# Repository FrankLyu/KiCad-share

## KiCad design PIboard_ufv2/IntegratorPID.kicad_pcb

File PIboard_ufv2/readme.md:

The hopefully final design works. With everything unchanged, the bandwidth is a bit low, only 2.5 kHz for full integral.

Now I changed the resistor for AD8429 to 680 Ohm, so the BW is now 5 kHz. (With default, it is 1.5kOhm, probably too large)

The test sequence:
First change TP-1H to very high, and change TP-1L to very low. Then with 50 Ohm ended on setpoint, another arm with controllable input:
	1. Check on TP4 the diff amp works.
	2. Short J12, check pure P works at TP5.
	3. Short J4, disconnect J12. It is a pure I. check it locks to itself.
	4. Solder bourns 1,2,3 pin to down, middle, and up pins.
	5. Change R32 to 10k if you want the manual out to start from 0 V, instead of some negative value.
	
Simple and nice!

There is a bug. The input signalIn and Setpoint are connected. When locked, SP is high but RF switch is overridden, then SignalIn (measurement) will be a non-zero value! When not locked, SP is low and manual out is high s.t. signalin is high, the measurement may be trimmed by the low SP. 
It can go to at most 4 V. However, if the SP is floating it will be okay?

Next version, we can Change R32 to a place where it is easier to resolder. It sets the lower limit of the manual output.

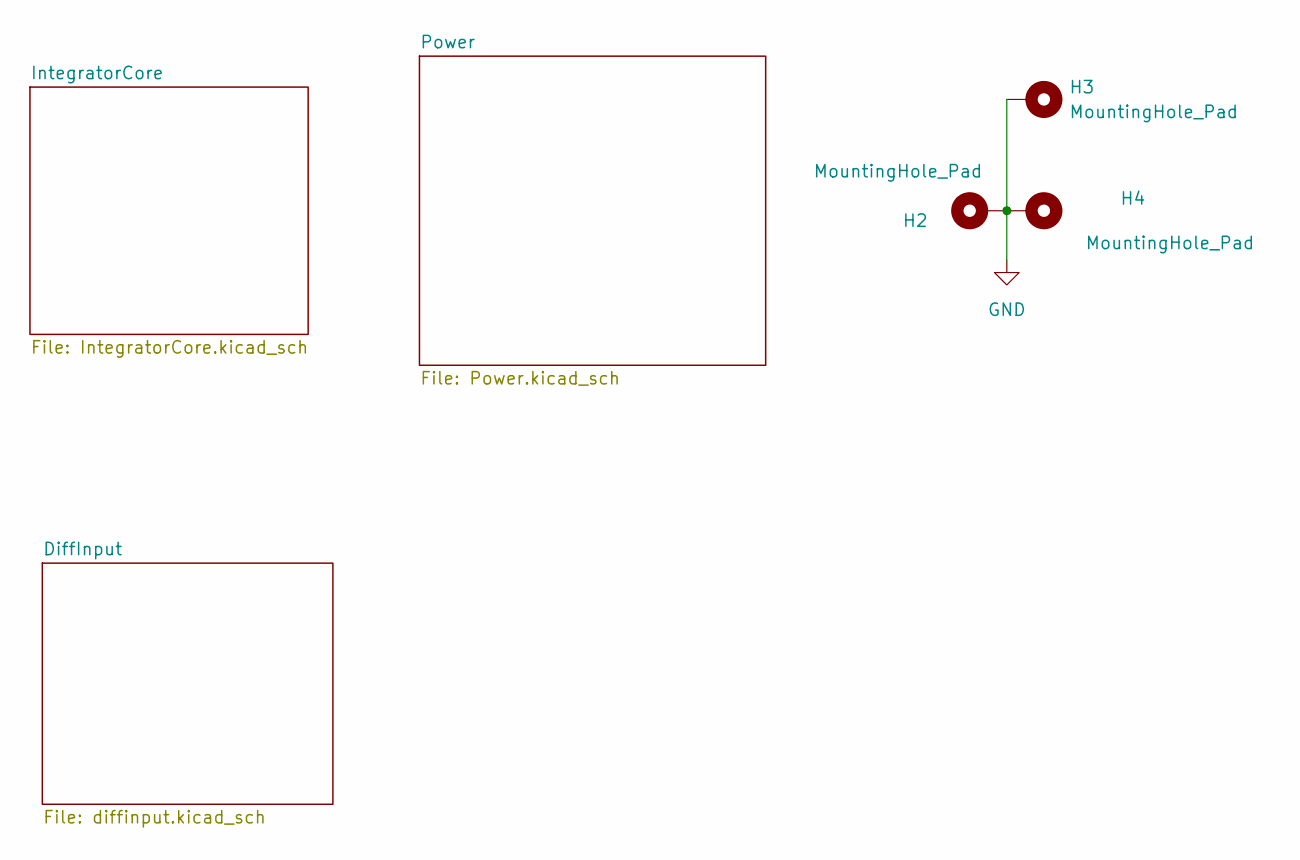
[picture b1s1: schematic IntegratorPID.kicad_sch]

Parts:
H2, H3, H4: MountingHole_Pad; MountingHole_3.7mm_Pad_Via

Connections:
GND: H2.1, H3.1, H4.1; also elsewhere on the board

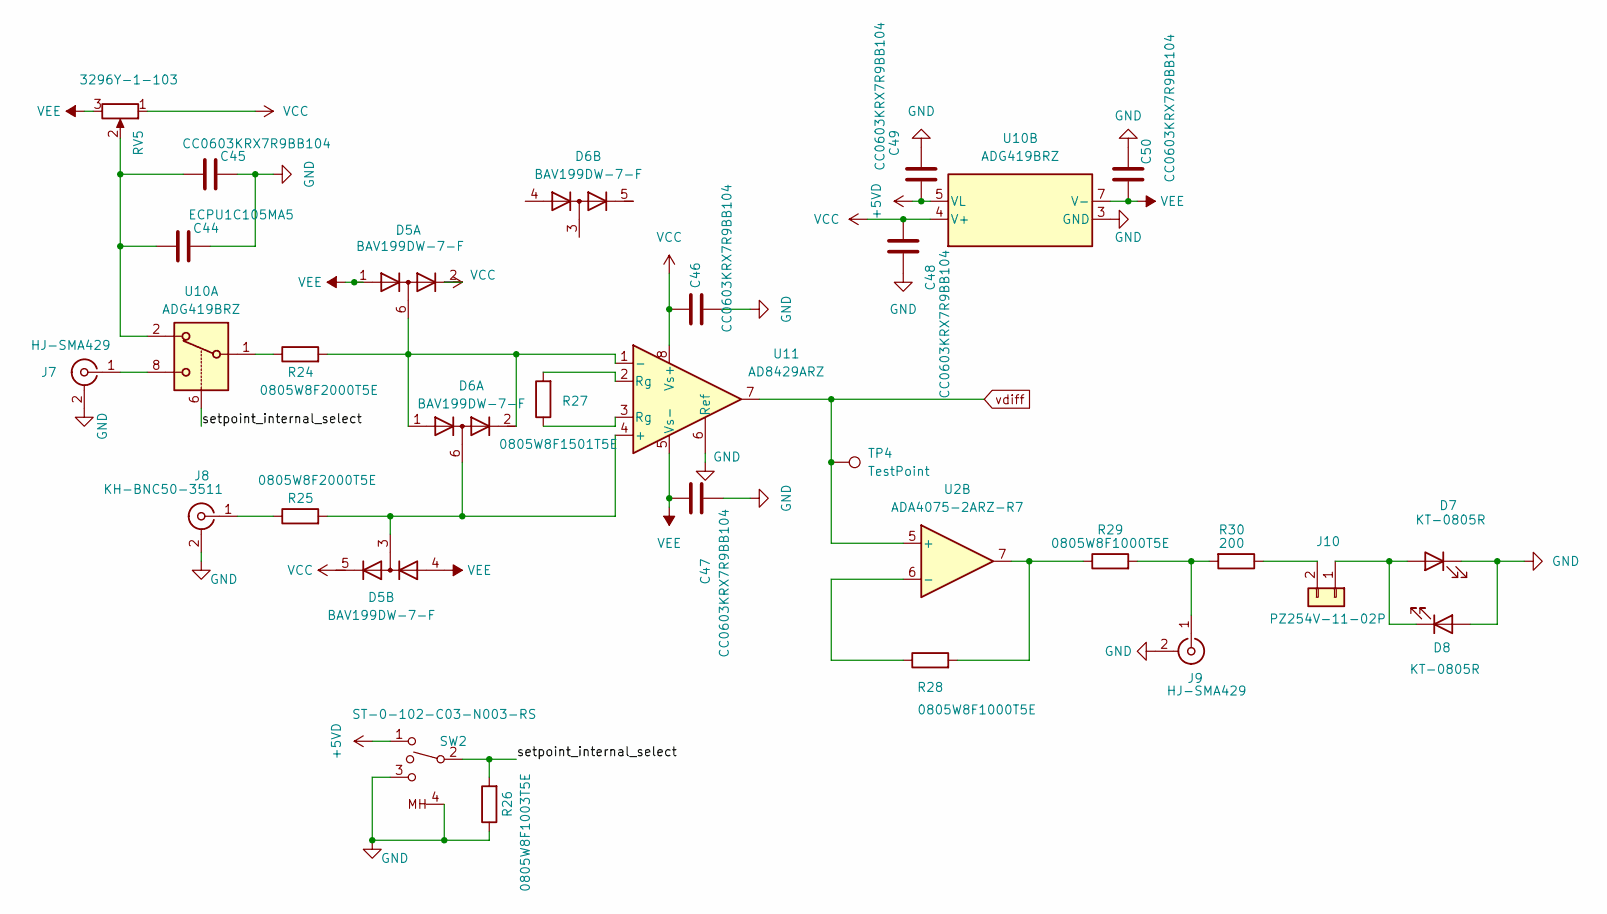
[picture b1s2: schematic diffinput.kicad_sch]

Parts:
C44: ECPU1C105MA5; C_1210_3225Metric_Pad1.33x2.70mm_HandSolder
C45, C46, C47, C48, C49, C50: CC0603KRX7R9BB104; C_0603_1608Metric_Pad1.08x0.95mm_HandSolder
D5, D6: BAV199DW-7-F; SOT-363_SC-70-6
D7, D8: KT-0805R; D_0805_2012Metric_Pad1.15x1.40mm_HandSolder
J7, J9: HJ-SMA429; SMA_Amphenol_132134_Vertical
J8: KH-BNC50-3511; BNC_Amphenol_B6252HB-NPP3G-50_Horizontal
J10: PZ254V-11-02P; PinHeader_1x02_P2.54mm_Vertical
R24, R25: 0805W8F2000T5E; R_0805_2012Metric
R26: 0805W8F1003T5E; R_0805_2012Metric
R27: 0805W8F1501T5E; R_0805_2012Metric
R28, R29: 0805W8F1000T5E; R_0805_2012Metric
R30: 200; R_0805_2012Metric
RV5: 3296Y-1-103; Potentiometer_Bourns_3296Y_Vertical
SW2: ST-0-102-C03-N003-RS; SW_SPDT_ST-0-103-C03-N003-RS
TP4: TestPoint; TestPoint_Pad_D1.0mm
U2: ADA4075-2ARZ-R7; SOIC-8_3.9x4.9mm_P1.27mm
U10: ADG419BRZ; SOIC-8_3.9x4.9mm_P1.27mm
U11: AD8429ARZ; SOIC-8_3.9x4.9mm_P1.27mm

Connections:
+5VD: C49.2, SW2.1, U10.5 (VL); also elsewhere on the board
/DiffInput/setpoint_internal_select: R26.2, SW2.2, U10.6
GND: C44.2, C45.2, C46.1, C47.1, C48.1, C49.1, C50.2, D7.1 (K), D8.2 (A), J7.2 (Ext), J8.2 (Ext), J9.2 (Ext), R26.1, SW2.3, SW2.4 (MH), U10.3 (GND), U11.6 (Ref); also elsewhere on the board
unnamed: C44.1, C45.1, RV5.2, U10.2
unnamed: D5.6 (K3A4), D6.1 (A1), D6.2 (K2), R24.2, U11.1 (-)
unnamed: D5.3 (K1A2), D6.6 (K3A4), R25.2, U11.4 (+)
unnamed: D7.2 (A), D8.1 (K), J10.1
unnamed: J7.1 (In), U10.8
unnamed: J8.1 (In), R25.1
unnamed: J9.1 (In), R29.2, R30.2
unnamed: J10.2, R30.1
unnamed: R24.1, U10.1
unnamed: R27.1, U11.3 (Rg)
unnamed: R27.2, U11.2 (Rg)
unnamed: R28.2, R29.1, U2.7
unnamed: R28.1, U2.6 (-)
VCC: C46.2, C48.2, D5.2 (K2), D5.5 (K4), RV5.1, U10.4 (V+), U11.8 (Vs+); also elsewhere on the board
VEE: C47.2, C50.1, D5.1 (A1), D5.4 (A3), RV5.3, U10.7 (V-), U11.5 (Vs-); also elsewhere on the board
vdiff: TP4.1, U2.5 (+), U11.7; also elsewhere on the board

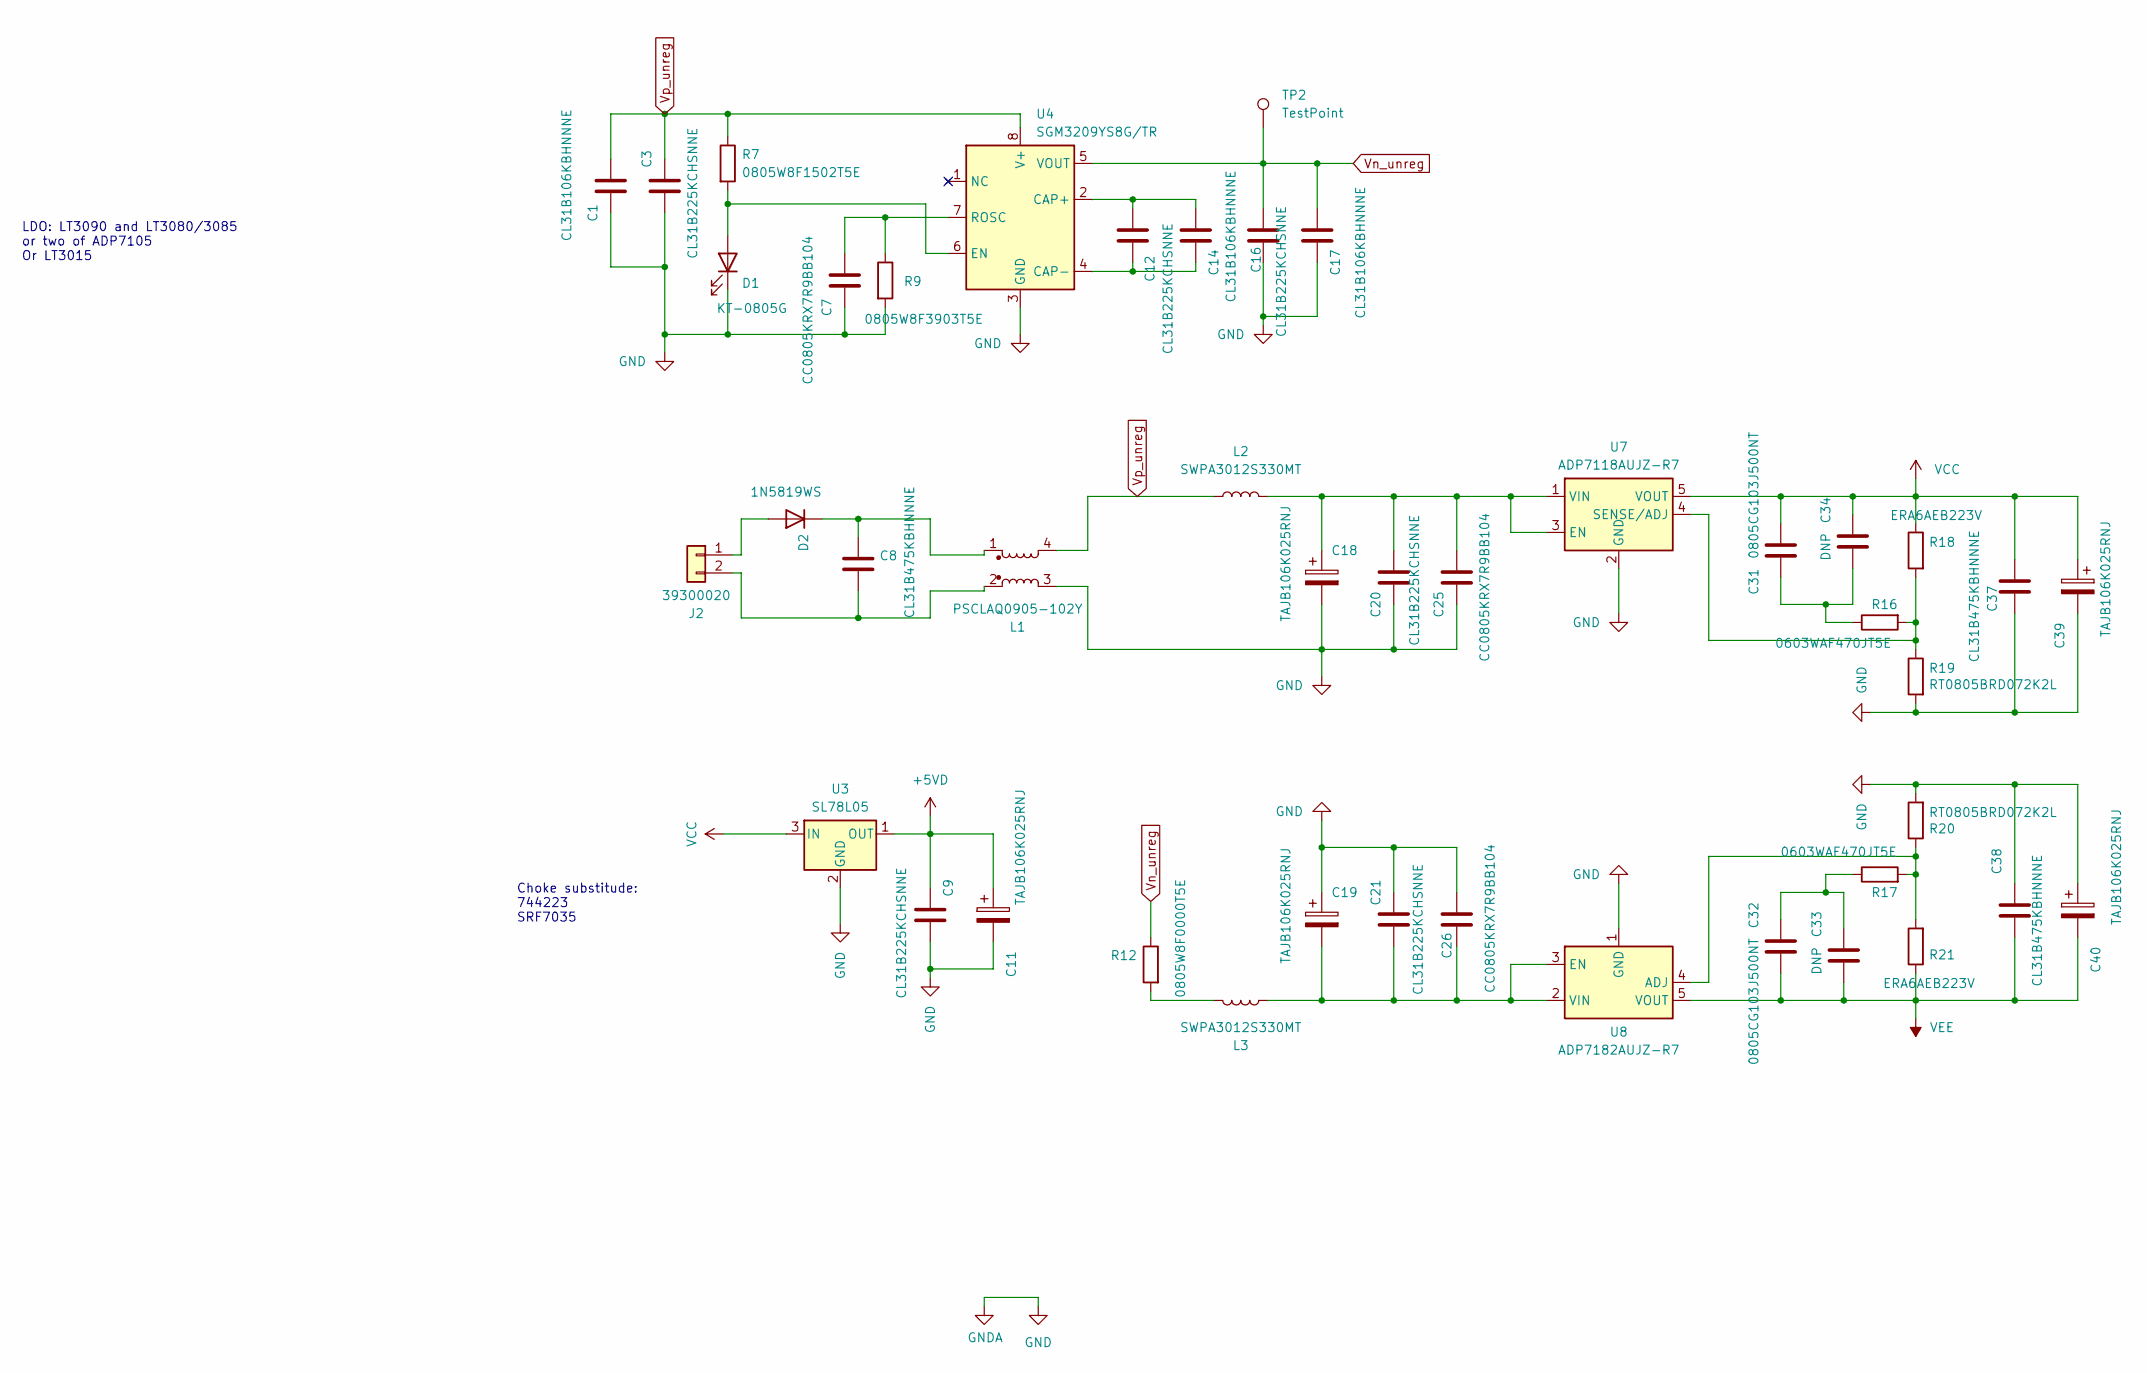
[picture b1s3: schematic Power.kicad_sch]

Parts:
C1, C14, C17: CL31B106KBHNNNE; C_1206_3216Metric_Pad1.33x1.80mm_HandSolder
C3, C9, C12, C16, C20, C21: CL31B225KCHSNNE; C_1206_3216Metric_Pad1.33x1.80mm_HandSolder
C7, C25, C26: CC0805KRX7R9BB104; C_0805_2012Metric
C8, C37, C38: CL31B475KBHNNNE; C_1206_3216Metric_Pad1.33x1.80mm_HandSolder
C11, C18, C19, C39, C40: TAJB106K025RNJ; CP_EIA-3528-15_AVX-H
C31, C32: 0805CG103J500NT; C_0805_2012Metric
C33, C34: DNP; C_0805_2012Metric
D1: KT-0805G; D_0805_2012Metric_Pad1.15x1.40mm_HandSolder
D2: 1N5819WS; D_SOD-323_HandSoldering
J2: 39300020; 39-30-Y020
L1: PSCLAQ0905-102Y; SRF0905501Y
L2, L3: SWPA3012S330MT; L_Taiyo-Yuden_MD-3030
R7: 0805W8F1502T5E; R_0805_2012Metric
R9: 0805W8F3903T5E; R_0805_2012Metric
R12: 0805W8F0000T5E; R_0805_2012Metric
R16, R17: 0603WAF470JT5E; R_0603_1608Metric_Pad0.98x0.95mm_HandSolder
R18, R21: ERA6AEB223V; R_0805_2012Metric
R19, R20: RT0805BRD072K2L; R_0805_2012Metric
TP2: TestPoint; TestPoint_Pad_D1.5mm
U3: SL78L05; SOT-89-3
U4: SGM3209YS8G/TR; SOIC-8_3.9x4.9mm_P1.27mm
U7: ADP7118AUJZ-R7; TSOT-23-5
U8: ADP7182AUJZ-R7; TSOT-23-5

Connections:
+5VD: C9.2, C11.1, U3.1 (OUT); also elsewhere on the board
GND: C1.2, C3.1, C7.2, C9.1, C11.2, C16.1, C17.2, C18.2, C19.1, C20.2, C21.2, C25.2, C26.2, C37.2, C38.2, C39.2, C40.1, D1.1 (K), L1.3, R9.2, R19.2, R20.2, U3.2 (GND), U4.3 (GND), U7.2 (GND), U8.1 (GND); also elsewhere on the board
unnamed: C31.2, C34.1, R16.1
unnamed: C32.2, C33.2, R17.1
unnamed: D1.2 (A), R7.2, U4.6 (EN)
unnamed: D2.2 (A), J2.1
unnamed: C8.1, D2.1 (K), L1.1
unnamed: C8.2, J2.2, L1.2
unnamed: L3.1, R12.2
unnamed: C12.2, C14.1, U4.2 (CAP+)
unnamed: C12.1, C14.2, U4.4 (CAP-)
unnamed: C7.1, R9.1, U4.7 (ROSC)
unnamed: C18.1, C20.1, C25.1, L2.2, U7.1 (VIN), U7.3 (EN)
unnamed: R16.2, R18.2, R19.1, U7.4 (SENSE/ADJ)
unnamed: R17.2, R20.1, R21.2, U8.4 (ADJ)
unnamed: C19.2, C21.1, C26.1, L3.2, U8.2 (VIN), U8.3 (EN)
VCC: C31.1, C34.2, C37.1, C39.1, R18.1, U3.3 (IN), U7.5 (VOUT); also elsewhere on the board
VEE: C32.1, C33.1, C38.1, C40.2, R21.1, U8.5 (VOUT); also elsewhere on the board
Vn_unreg: C16.2, C17.1, R12.1, TP2.1, U4.5 (VOUT)
Vp_unreg: C1.1, C3.2, L1.4, L2.1, R7.1, U4.8 (V+)

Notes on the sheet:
Choke substitude: 744223 SRF7035
LDO: LT3090 and LT3080/3085 or two of ADP7105 Or LT3015

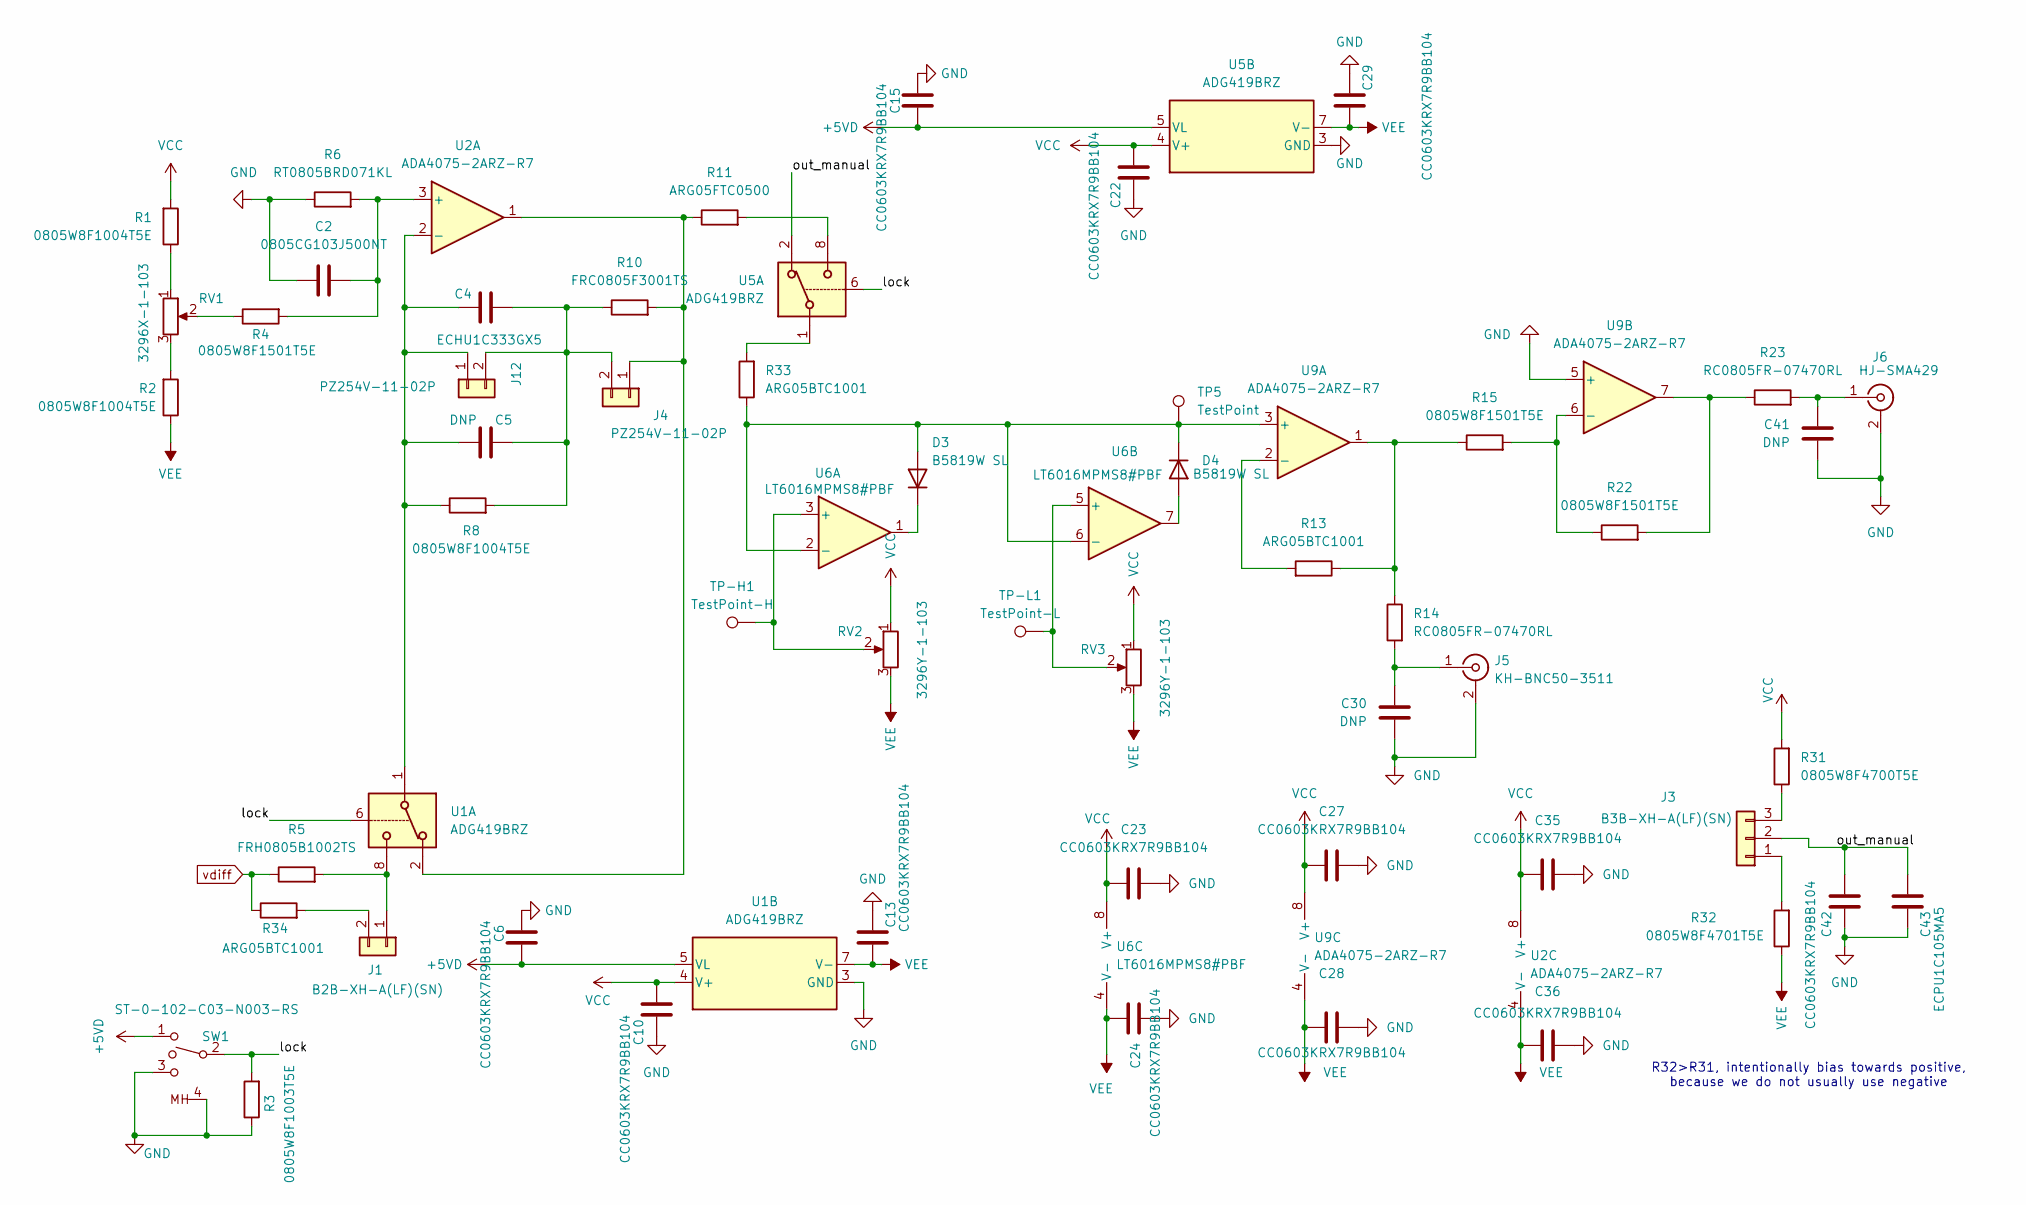
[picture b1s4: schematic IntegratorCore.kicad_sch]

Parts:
C2: 0805CG103J500NT; C_0805_2012Metric
C4: ECHU1C333GX5; C_1206_3216Metric
C5: DNP; C_2225_5664Metric_Pad1.80x6.60mm_HandSolder
C6, C10, C13, C15, C22, C23, C24, C27, C28, C29, C35, C36, C42: CC0603KRX7R9BB104; C_0603_1608Metric_Pad1.08x0.95mm_HandSolder
C30, C41: DNP; C_0805_2012Metric
C43: ECPU1C105MA5; C_1210_3225Metric_Pad1.33x2.70mm_HandSolder
D3, D4: B5819W SL; D_SOD-123
J1: B2B-XH-A(LF)(SN); JST_XH_B2B-XH-A_1x02_P2.50mm_Vertical
J3: B3B-XH-A(LF)(SN); JST_XH_B3B-XH-A_1x03_P2.50mm_Vertical
J4, J12: PZ254V-11-02P; PinHeader_1x02_P2.54mm_Vertical
J5: KH-BNC50-3511; BNC_Amphenol_B6252HB-NPP3G-50_Horizontal
J6: HJ-SMA429; SMA_Amphenol_132134_Vertical
R1, R2, R8: 0805W8F1004T5E; R_0805_2012Metric
R3: 0805W8F1003T5E; R_0805_2012Metric
R4, R15, R22: 0805W8F1501T5E; R_0805_2012Metric
R5: FRH0805B1002TS; R_0805_2012Metric
R6: RT0805BRD071KL; R_0805_2012Metric
R10: FRC0805F3001TS; R_0805_2012Metric
R11: ARG05FTC0500; R_0805_2012Metric
R13, R33, R34: ARG05BTC1001; R_0805_2012Metric
R14, R23: RC0805FR-07470RL; R_0805_2012Metric
R31: 0805W8F4700T5E; R_0805_2012Metric
R32: 0805W8F4701T5E; R_0805_2012Metric
RV1: 3296X-1-103; Potentiometer_Bourns_3296X_Horizontal
RV2, RV3: 3296Y-1-103; Potentiometer_Bourns_3296Y_Vertical
SW1: ST-0-102-C03-N003-RS; SW_SPDT_ST-0-103-C03-N003-RS
TP5: TestPoint; TestPoint_Pad_D1.0mm
TP-H1: TestPoint-H; TestPoint_Pad_D1.0mm
TP-L1: TestPoint-L; TestPoint_Pad_D1.0mm
U1, U5: ADG419BRZ; SOIC-8_3.9x4.9mm_P1.27mm
U2, U9: ADA4075-2ARZ-R7; SOIC-8_3.9x4.9mm_P1.27mm
U6: LT6016MPMS8#PBF; MSOP-8_3x3mm_P0.65mm

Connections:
+5VD: C6.2, C15.2, SW1.1, U1.5 (VL), U5.5 (VL); also elsewhere on the board
/IntegratorCore/lock: R3.2, SW1.2, U1.6, U5.6
/IntegratorCore/out_manual: C42.1, C43.1, J3.2, U5.2
GND: C2.1, C6.1, C10.2, C13.2, C15.1, C22.2, C23.1, C24.1, C27.1, C28.1, C29.2, C30.1, C35.1, C36.1, C41.1, C42.2, C43.2, J5.2 (Ext), J6.2 (Ext), R3.1, R6.1, SW1.3, SW1.4 (MH), U1.3 (GND), U5.3 (GND), U9.5 (+); also elsewhere on the board
unnamed: D3.2 (A), D4.1 (K), R33.1, TP5.1, U6.2 (-), U6.6 (-), U9.3 (+)
unnamed: D3.1 (K), U6.1
unnamed: D4.2 (A), U6.7
unnamed: J1.1, R5.2, U1.8
unnamed: J1.2, R34.2
unnamed: J3.1, R32.2
unnamed: J3.3, R31.1
unnamed: J4.1, R10.2, R11.1, U1.2, U2.1
unnamed: C30.2, J5.1 (In), R14.2
unnamed: C41.2, J6.1 (In), R23.2
unnamed: C4.1, C5.1, J12.1, R8.1, U1.1, U2.2 (-)
unnamed: C4.2, C5.2, J4.2, J12.2, R8.2, R10.1
unnamed: R1.1, RV1.1
unnamed: R2.2, RV1.3
unnamed: R4.1, RV1.2
unnamed: R11.2, U5.8
unnamed: R13.1, R14.1, R15.1, U9.1
unnamed: R22.2, R23.1, U9.7
unnamed: R33.2, U5.1
unnamed: C2.2, R4.2, R6.2, U2.3 (+)
unnamed: RV2.2, TP-H1.1, U6.3 (+)
unnamed: RV3.2, TP-L1.1, U6.5 (+)
unnamed: R13.2, U9.2 (-)
unnamed: R15.2, R22.1, U9.6 (-)
VCC: C10.1, C22.1, C23.2, C27.2, C35.2, R1.2, R31.2, RV2.1, RV3.1, U1.4 (V+), U2.8 (V+), U5.4 (V+), U6.8 (V+), U9.8 (V+); also elsewhere on the board
VEE: C13.1, C24.2, C28.2, C29.1, C36.2, R2.1, R32.1, RV2.3, RV3.3, U1.7 (V-), U2.4 (V-), U5.7 (V-), U6.4 (V-), U9.4 (V-); also elsewhere on the board
vdiff: R5.1, R34.1; also elsewhere on the board

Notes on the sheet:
R32>R31, intentionally bias towards positive, because we do not usually use negative

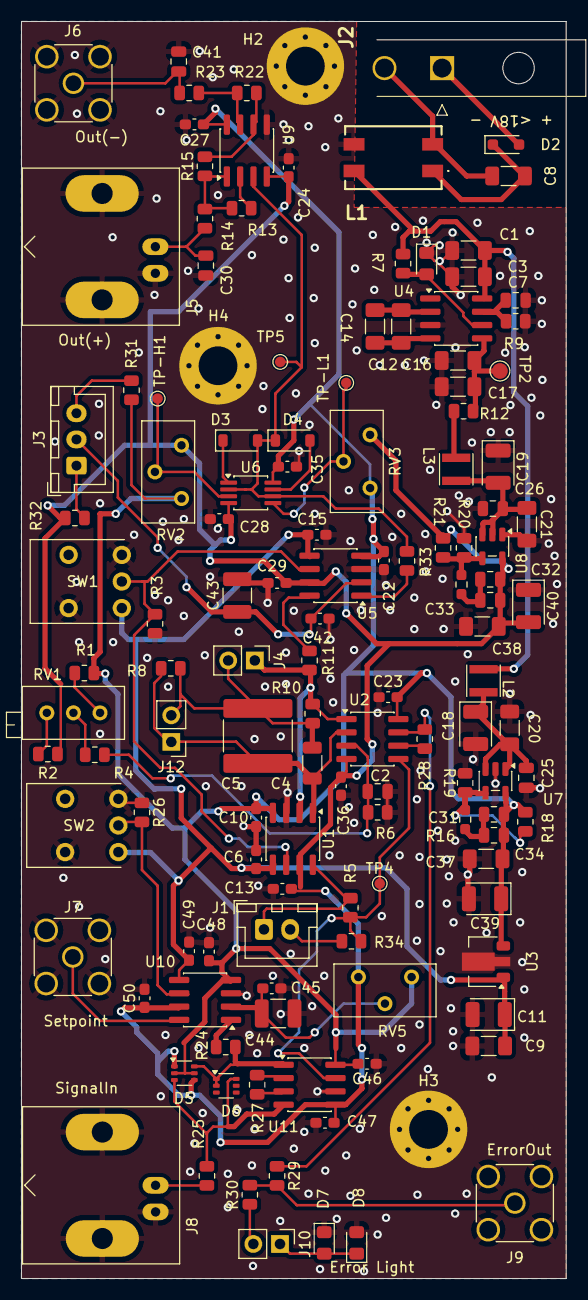
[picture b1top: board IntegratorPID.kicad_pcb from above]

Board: 4 copper layers, 52.0 x 120.0 mm, 131 parts (0 on the bottom side), 61 nets.

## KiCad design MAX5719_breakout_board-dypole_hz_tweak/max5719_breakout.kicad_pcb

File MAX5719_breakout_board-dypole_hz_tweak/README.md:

Teensy MAX5719 high-resolution (low-speed) AWG v1 in dypole. Problems are at the bottom of the file.

Interface is via SPI, all microcontroller signals are isolated using MAX14850ASE (or compatible) capacitive isolator. A galvanically isolated power supply may be used to provide the +/-15V DAC/analog buffer supply, so microcontroller USB does not need to be isolated.
Tested up to 20MHz SPI on a breadboard, good layout of microcontroller to breakout board PCB may allow for higher speeds (MAX5719 is specified up to 50MHz).

Onboard 5 V voltage reference, output is then scaled up by 2.0x for a 10V range.

JP1 is for unipolar output. JP2/3 for bipolar.

We chose Op Amp OP2192. Voltage reference chip MAX6126 (which has a demo schematic for MAX5719). The exact voltages on board should be +13.2, -13.2 and +5.376 V.

Production (purchased at JLCPCB) on Sep 9th 2025. This version has 3 problems. 

First, the zero resistors are not soldered. The voltage divider (resistor) for ADP7118 5 V is wrong.

Second, the +13.2 V and -13.2 V fight each other. Negative prevents positive voltage from turning on. This might be the safe feature of ADP7118. After taking away the OP2192, the problem is gone.

Third, the BNC connector is not well shielded, and it picks up high frequency (>10 MHz RF) from the air.

To address the second problem, we go back to LM7812, LM7912 to power the Op amp. It doesn't affect the noise performance.

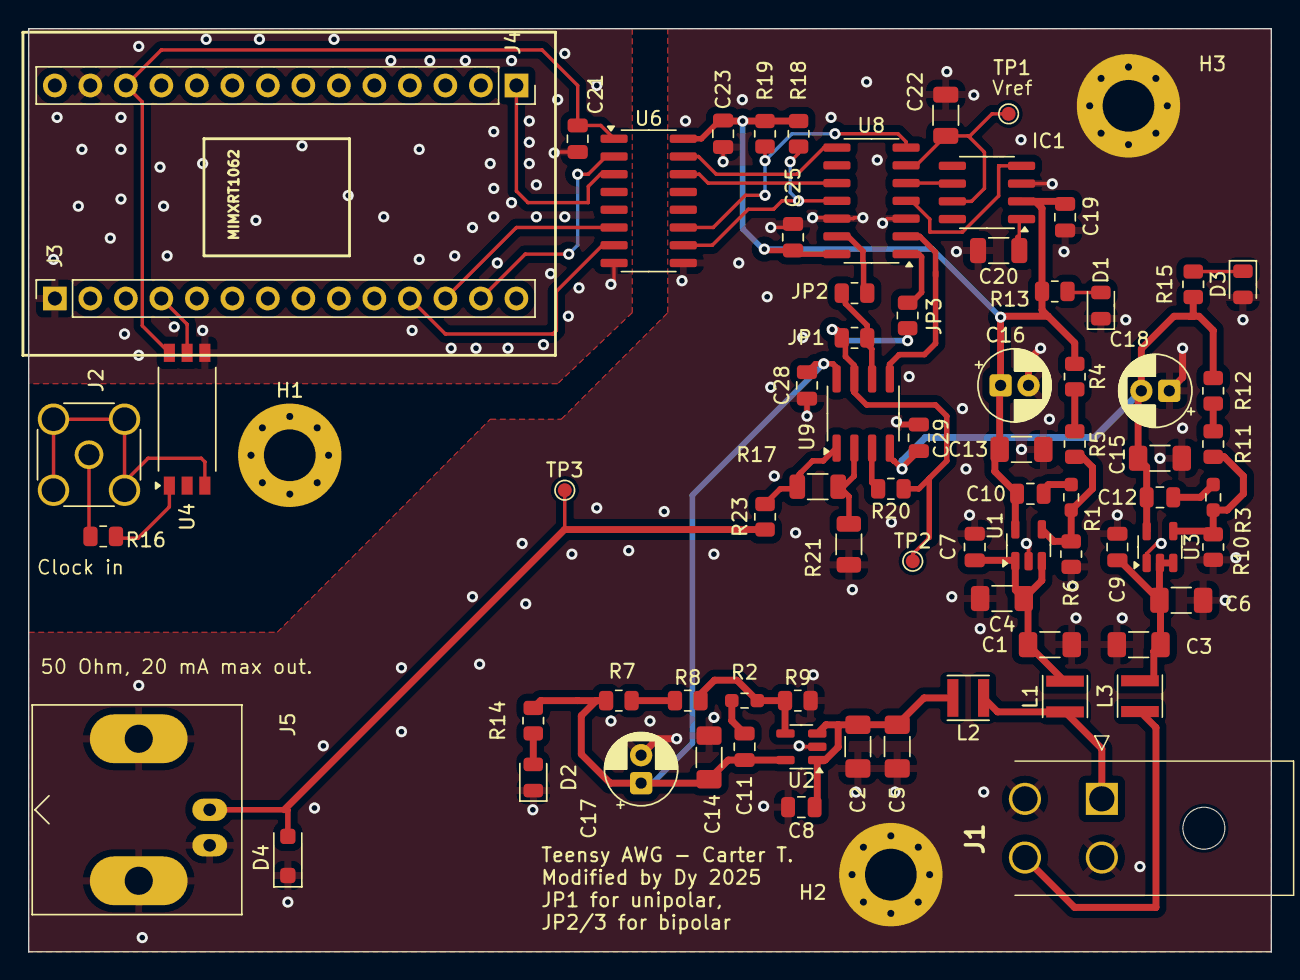
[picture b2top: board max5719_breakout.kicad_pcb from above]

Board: 4 copper layers, 88.9 x 66.0 mm, 77 parts (0 on the bottom side), 48 nets.

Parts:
C1, C2, C3, C4, C5, C6, C13, C14, C15: 1206B475K500NT; C_1206_3216Metric_Pad1.33x1.80mm_HandSolder
C7, C8, C9, C19, C21, C23, C25, C28, C29: CC0805KRX7R9BB104; C_0805_2012Metric
C10, C11, C12: 0805CG103J500NT; C_0805_2012Metric
C16, C17, C18: HG1H226M0508PC; CP_Radial_D5.0mm_P2.00mm
C20, C22: CGA5L2C0G1H104JT0Y0N; C_1206_3216Metric
D1, D2, D3: C2297; LED_0805_2012Metric
D4: SMF12CA; D_SOD-123F
H1, H2, H3: MountingHole_Pad; MountingHole_3.7mm_Pad_Via
IC1: MAX6126AASA50+; SOIC-8_3.9x4.9mm_P1.27mm
J1: 39300040; 39-30-Y040
J2: HJ-SMA429; SMA_Amphenol_132134-16_Vertical
J3, J4: PM254-1-14-Z-8.5; PinSocket_1x14_P2.54mm_Vertical
J5: KH-BNC50-3511; BNC_Amphenol_B6252HB-NPP3G-50_Horizontal
JP1: 0805W8F0000T5E; R_0805_2012Metric
JP2, JP3: DNP; R_0805_2012Metric
L1, L2, L3: SWPA3015S330MT; L_Taiyo-Yuden_MD-3030
R1, R2, R3: 0603WAF470JT5E; R_0603_1608Metric_Pad0.98x0.95mm_HandSolder
R4: ARG05BTC3481; R_0805_2012Metric
R5, R7, R12: 0805W8F0000T5E; R_0805_2012Metric
R6: AR05BTCW3502; R_0805_2012Metric
R8, R11, R14, R15: 0805W8F1003T5E; R_0805_2012Metric
R9, R10: 0805W8F1002T5E; R_0805_2012Metric
R13: 0805W8F3162T5E; R_0805_2012Metric
R16: 0805W8F6800T5E; R_0805_2012Metric
R17, R21: ARG06BTC1001; R_1206_3216Metric
R18, R19: PTFR0805B1K00N9; R_0805_2012Metric
R20: 0805W8F1000T5E; R_0805_2012Metric
R23: AR05FTBW0500; R_0805_2012Metric
TP1: Ref; TestPoint_Pad_D1.0mm
TP2: Out/2.5; TestPoint_Pad_D1.0mm
TP3: Out; TestPoint_Pad_D1.0mm
U1, U2: ADP7118AUJZ-R7; TSOT-23-5
U3: ADP7182AUJZ-R7; TSOT-23-5
U4: TLP2770(TP,E; SO-6L_10x3.84mm_P1.27mm
U6: MAX14850ASE+; SOIC-16_3.9x9.9mm_P1.27mm
U8: MAX5719AGSD+; SOIC-14_3.9x8.7mm_P1.27mm
U9: OPA2192IDR; SOIC-8_3.9x4.9mm_P1.27mm

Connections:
+3.3V: C21.1, J4.12, U4.6 (VDD), U6.1 (VCCA)
+5V: C10.1, C13.1, C16.1, C19.2, C23.1, C25.2, IC1.2 (IN), R4.1, R13.1, R18.1, R19.1, U1.5 (VOUT), U6.16 (VCCB), U8.14 (VDD)
+12V: C11.1, C14.1, C17.1, C28.1, R7.1, R14.1, U2.5 (VOUT), U9.8 (V+)
-12V: C12.1, C15.1, C18.2, C29.1, R12.1, R15.1, U3.5 (VOUT), U9.4 (V-)
/core/CS: J3.12, U6.6 (I/OA1)
/core/DIN: J4.1, U6.3 (INA2)
/core/GNDS: IC1.4 (GNDS), U8.4 (AGNDS)
/core/LDAC: J3.11, U6.7 (I/OA2)
/core/REF_F: C22.1, IC1.7 (OUTF), TP1.1, U8.6 (REFF)
/core/REF_S: IC1.6 (OUTS), U8.5 (REFS)
/core/SCLK: J3.13, U6.2 (INA1)
GND: C1.2, C2.2, C3.2, C4.2, C5.2, C6.2, C7.2, C8.2, C9.2, C13.2, C14.2, C15.2, C16.2, C17.2, C18.1, C19.1, C20.2, C22.2, C23.2, C25.1, C28.2, C29.2, D1.1 (K), D2.1 (K), D3.2 (A), D4.1 (A1), H2.1, H3.1, IC1.3 (GND), J1.2, J1.3, J5.2 (Ext), R6.2, R9.2, R10.1, R21.2, U1.2 (GND), U2.2 (GND), U3.1 (GND), U6.9 (GNDB), U8.3 (AGNDF), U8.12 (DGND)
GNDD: C21.2, J3.1, J4.13, U4.4 (GND), U6.8 (GNDA)
unnamed: C10.2, R1.1
unnamed: C11.2, R2.1
unnamed: C12.2, R3.1
unnamed: D1.2 (A), R13.2
unnamed: D2.2 (A), R14.2
unnamed: D3.1 (K), R15.2
unnamed: D4.2 (A2), J5.1 (In), R23.2, TP3.1
unnamed: C20.1, IC1.1 (NR)
unnamed: J2.2 (Ext), U4.3 (K)
unnamed: J2.1 (In), R16.1
unnamed: J3.4, U4.5 (VO)
unnamed: JP1.1 (A), JP2.2 (B), U9.6 (-)
unnamed: JP1.2 (B), JP3.1 (A), R20.2, TP2.1, U9.7
unnamed: JP2.1 (A), U8.13 (INV)
unnamed: JP3.2 (B), U8.1 (RFB)
unnamed: R4.2, R5.1
unnamed: R7.2, R8.1
unnamed: R11.1, R12.2
unnamed: R17.1, R23.1, U9.1
unnamed: C1.1, C4.1, C7.1, L1.2, U1.1 (VIN), U1.3 (EN)
unnamed: R1.2, R5.2, R6.1, U1.4 (SENSE/ADJ)
unnamed: C2.1, C5.1, C8.1, L2.2, U2.1 (VIN), U2.3 (EN)
unnamed: R2.2, R8.2, R9.1, U2.4 (SENSE/ADJ)
unnamed: R3.2, R10.2, R11.2, U3.4 (ADJ)
unnamed: C3.1, C6.1, C9.1, L3.2, U3.2 (VIN), U3.3 (EN)
unnamed: R16.2, U4.1 (A)
unnamed: R19.2, U6.11 (I/OB1), U8.7 (~CS)
unnamed: R18.2, U6.10 (I/OB2), U8.11 (~LDAC)
unnamed: U6.15 (OUTB1), U8.8 (SCLK)
unnamed: U6.14 (OUTB2), U8.10 (DIN)
unnamed: U8.2 (OUT), U9.5 (+)
unnamed: R20.1, U9.3 (+)
unnamed: R17.2, R21.1, U9.2 (-)
Vn_unreg: J1.4, L3.1
Vp_unreg: J1.1, L1.1, L2.1

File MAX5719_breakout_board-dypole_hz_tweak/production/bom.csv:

Designator,Footprint,Quantity,Value,LCSC Part #
"C1, C13, C14, C15, C2, C3, C4, C5, C6",1206,9,1206B475K500NT,
"C10, C11, C12",0805,3,0805CG103J500NT,
"C16, C17, C18",CP_Radial_D5.0mm_P2.00mm,3,HG1H226M0508PC,
"C19, C21, C23, C25, C28, C29, C7, C8, C9",0805,9,CC0805KRX7R9BB104,
"C20, C22",1206,2,CGA5L2C0G1H104JT0Y0N,
"D1, D2, D3",0805,3,C2297,
D4,D_SOD-123F,1,SMF12CA,
IC1,SOIC-8_3.9x4.9mm_P1.27mm,1,MAX6126AASA50+,
J1,39-30-Y040,1,39300040,
J2,SMA_Amphenol_132134-16_Vertical,1,HJ-SMA429,
"J3, J4",PinSocket_1x14_P2.54mm_Vertical,2,PM254-1-14-Z-8.5,
J5,BNC_Amphenol_B6252HB-NPP3G-50_Horizontal,1,KH-BNC50-3511,
"JP1, R12, R5, R7",0805,4,0805W8F0000T5E,
"JP2, JP3",0805,2,DNP,
"L1, L2, L3",L_Taiyo-Yuden_MD-3030,3,SWPA3015S330MT,
"R1, R2, R3",0603,3,0603WAF470JT5E,
"R10, R9",0805,2,0805W8F1002T5E,
"R11, R14, R15, R8",0805,4,0805W8F1003T5E,
R13,0805,1,0805W8F3162T5E,
R16,0805,1,0805W8F6800T5E,
"R17, R21",1206,2,ARG06BTC1001,
"R18, R19",0805,2,PTFR0805B1K00N9,
R20,0805,1,0805W8F1000T5E,
R23,0805,1,AR05FTBW0500,
R4,0805,1,ARG05BTC3481,
R6,0805,1,AR05BTCW3502,
TP1,TestPoint_Pad_D1.0mm,1,Ref,
TP2,TestPoint_Pad_D1.0mm,1,Out/2.5,
TP3,TestPoint_Pad_D1.0mm,1,Out,
"U1, U2",TSOT-23-5,2,ADP7118AUJZ-R7,
U3,TSOT-23-5,1,ADP7182AUJZ-R7,
U4,SO-6L_10x3.84mm_P1.27mm,1,"TLP2770(TP,E",
U6,SOIC-16_3.9x9.9mm_P1.27mm,1,MAX14850ASE+,
U8,SOIC-14_3.9x8.7mm_P1.27mm,1,MAX5719AGSD+,
U9,SOIC-8_3.9x4.9mm_P1.27mm,1,OPA2192IDR,

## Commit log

2025-09-10 Add files
2025-09-10 delete
2025-09-26 Version 2 production on 09/24/2025
